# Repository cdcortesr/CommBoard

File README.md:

## Communication Board (CommBoard)
<picture>
  <source media="(prefers-color-scheme: dark)" srcset="https://i.imgur.com/UVEQvyd.jpeg">
  <source media="(prefers-color-scheme: light)" srcset="https://i.imgur.com/UVEQvyd.jpeg">
  
</picture>

Self-built serial communication board based on an STM32 microcontroller, designed for embedded systems applications. Key features and technical details include:

• Communication Interfaces:

&nbsp;&nbsp;&nbsp;&nbsp;• I²C (Inter-Integrated Circuit) interface for peripheral connectivity.

&nbsp;&nbsp;&nbsp;&nbsp;• UART (Universal Asynchronous Receiver-Transmitter) for serial communication.

&nbsp;&nbsp;&nbsp;&nbsp;• JTAG interface for in-circuit programming and debugging.

&nbsp;&nbsp;&nbsp;&nbsp;• USB for data transfer and power input.

• PCB Design and Manufacturing:

&nbsp;&nbsp;&nbsp;&nbsp;• Dual-layer printed circuit board (PCB) designed using KiCad.

&nbsp;&nbsp;&nbsp;&nbsp;• Fabricated by JLCPCB (PCB manufacturer).

&nbsp;&nbsp;&nbsp;&nbsp;• Self-assembled using a combination of reflow oven soldering and manual hand soldering techniques.

• Power Supply:

&nbsp;&nbsp;&nbsp;&nbsp;• Powered via USB connection.

&nbsp;&nbsp;&nbsp;&nbsp;• Integrated Low Dropout Regulator (LDO) for stable voltage supply.

This project demonstrates proficiency in hardware design, embedded programming, and hands-on electronics assembly.

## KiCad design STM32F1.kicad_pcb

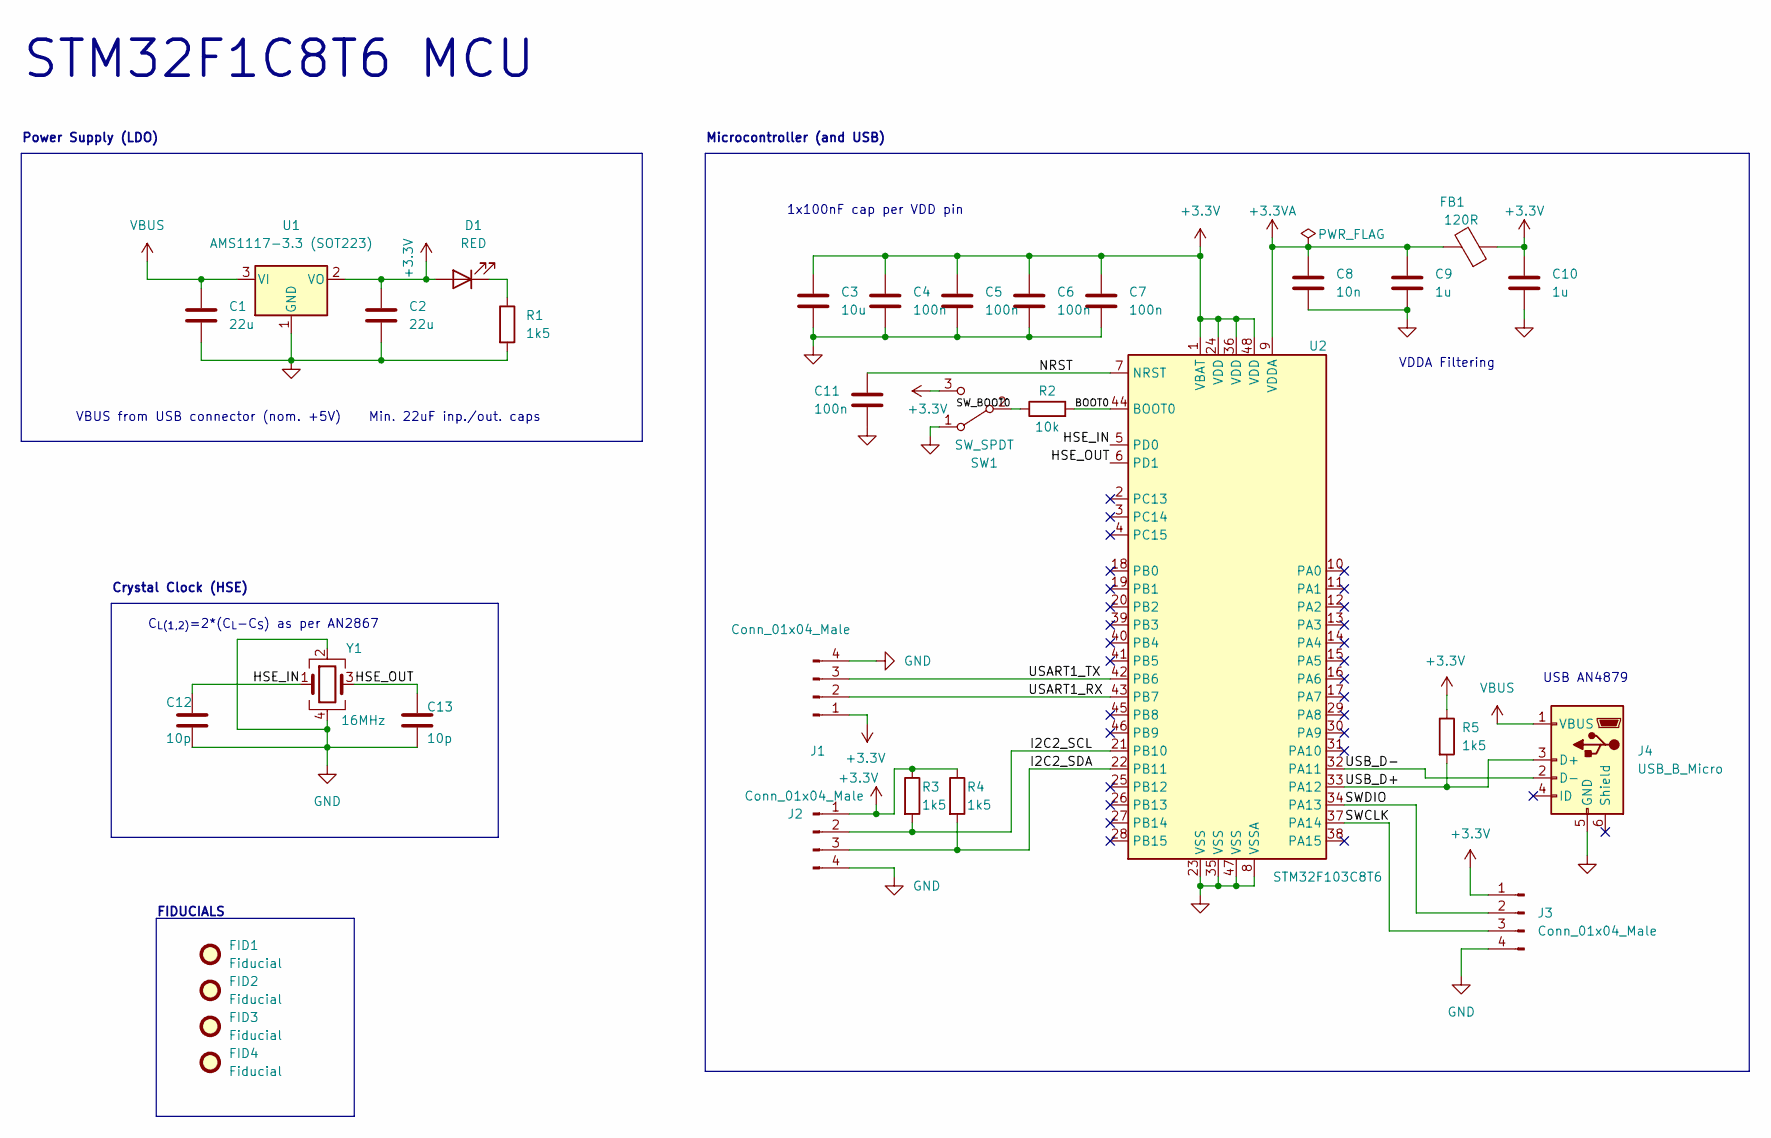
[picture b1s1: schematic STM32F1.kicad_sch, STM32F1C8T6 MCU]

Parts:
C1, C2: 22u; C_0805_2012Metric
C3: 10u; C_0603_1608Metric
C4, C5, C6, C7, C11: 100n; C_0402_1005Metric
C8: 10n; C_0603_1608Metric
C9, C10: 1u; C_0402_1005Metric
C12, C13: 10p; C_0402_1005Metric
D1: RED; LED_0603_1608Metric
FB1: 120R; L_0201_0603Metric
FID1, FID2, FID3, FID4: Fiducial; Fiducial_1mm_Mask2mm
J1, J2, J3: Conn_01x04_Male; PinHeader_1x04_P2.54mm_Vertical
J4: USB_B_Micro; USB_Micro-B_Wuerth_629105150521
R1, R3, R4, R5: 1k5; R_0402_1005Metric
R2: 10k; R_0402_1005Metric
SW1: SW_SPDT; SW_JS102011SAQN
U1: AMS1117-3.3 (SOT223); SOT-223-3_TabPin2
U2: STM32F103C8T6; LQFP-48_7x7mm_P0.5mm
Y1: 16MHz; Crystal_SMD_3225-4Pin_3.2x2.5mm

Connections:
+3.3VA: C8.1, C9.1, FB1.2, U2.9 (VDDA)
+3V3: C2.1, C3.1, C4.1, C5.1, C6.1, C7.1, C10.1, D1.2 (A), FB1.1, J1.1, J2.1, J3.1, R3.1, R4.1, R5.1, SW1.3 (C), U1.2 (VO), U2.1 (VBAT), U2.24 (VDD), U2.36 (VDD), U2.48 (VDD)
/BOOT0: R2.2, U2.44 (BOOT0)
/HSE_IN: C12.1, U2.5 (PD0), Y1.1
/HSE_OUT: C13.1, U2.6 (PD1), Y1.3
/I2C2_SCL: J2.2, R3.2, U2.21 (PB10)
/I2C2_SDA: J2.3, R4.2, U2.22 (PB11)
/NRST: C11.1, U2.7 (NRST)
/SWCLK: J3.3, U2.37 (PA14)
/SWDIO: J3.2, U2.34 (PA13)
/SW_BOOT0: R2.1, SW1.2 (B)
/USART1_RX: J1.2, U2.43 (PB7)
/USART1_TX: J1.3, U2.42 (PB6)
/USB_D+: J4.3 (D+), R5.2, U2.33 (PA12)
/USB_D-: J4.2 (D-), U2.32 (PA11)
GND: C1.2, C2.2, C3.2, C4.2, C5.2, C6.2, C7.2, C8.2, C9.2, C10.2, C11.2, C12.2, C13.2, J1.4, J2.4, J3.4, J4.5 (GND), R1.2, SW1.1 (A), U1.1 (GND), U2.8 (VSSA), U2.23 (VSS), U2.35 (VSS), U2.47 (VSS), Y1.2, Y1.4
unnamed: D1.1 (K), R1.1
VBUS: C1.1, J4.1 (VBUS), U1.3 (VI)

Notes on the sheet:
1x100nF cap per VDD pin
Power Supply (LDO)
${TITLE}
VDDA Filtering
Crystal Clock (HSE)
FIDUCIALS
Microcontroller (and USB)
VBUS from USB connector (nom. +5V) Min. 22uF inp./out. caps
C_{L(1,2)}=2*(C_{L}-C_{S}) as per AN2867
USB AN4879

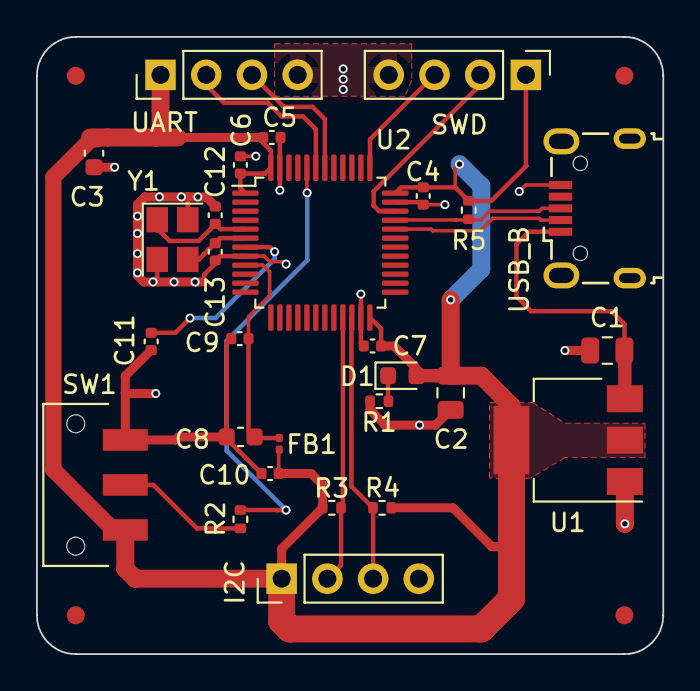
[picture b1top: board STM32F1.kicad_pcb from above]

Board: 2 copper layers, 34.8 x 34.3 mm, 32 parts (0 on the bottom side), 18 nets.

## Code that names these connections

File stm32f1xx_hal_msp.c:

/* USER CODE BEGIN Header */
/**
  ******************************************************************************
  * @file         stm32f1xx_hal_msp.c
  * @brief        This file provides code for the MSP Initialization
  *               and de-Initialization codes.
  ******************************************************************************
  * @attention
  *
  * Copyright (c) 2023 STMicroelectronics.
  * All rights reserved.
  *
  * This software is licensed under terms that can be found in the LICENSE file
  * in the root directory of this software component.
  * If no LICENSE file comes with this software, it is provided AS-IS.
  *
  ******************************************************************************
  */
/* USER CODE END Header */

/* Includes ------------------------------------------------------------------*/
#include "main.h"

/* USER CODE BEGIN Includes */

/* USER CODE END Includes */

/* Private typedef -----------------------------------------------------------*/
/* USER CODE BEGIN TD */

/* USER CODE END TD */

/* Private define ------------------------------------------------------------*/
/* USER CODE BEGIN Define */

/* USER CODE END Define */

/* Private macro -------------------------------------------------------------*/
/* USER CODE BEGIN Macro */

/* USER CODE END Macro */

/* Private variables ---------------------------------------------------------*/
/* USER CODE BEGIN PV */

/* USER CODE END PV */

/* Private function prototypes -----------------------------------------------*/
/* USER CODE BEGIN PFP */

/* USER CODE END PFP */

/* External functions --------------------------------------------------------*/
/* USER CODE BEGIN ExternalFunctions */

/* USER CODE END ExternalFunctions */

/* USER CODE BEGIN 0 */

/* USER CODE END 0 */
/**
  * Initializes the Global MSP.
  */
void HAL_MspInit(void)
{
  /* USER CODE BEGIN MspInit 0 */

  /* USER CODE END MspInit 0 */

  __HAL_RCC_AFIO_CLK_ENABLE();
  __HAL_RCC_PWR_CLK_ENABLE();

  /* System interrupt init*/

  /** NOJTAG: JTAG-DP Disabled and SW-DP Enabled
  */
  __HAL_AFIO_REMAP_SWJ_NOJTAG();

  /* USER CODE BEGIN MspInit 1 */

  /* USER CODE END MspInit 1 */
}

/**
* @brief I2C MSP Initialization
* This function configures the hardware resources used in this example
* @param hi2c: I2C handle pointer
* @retval None
*/
void HAL_I2C_MspInit(I2C_HandleTypeDef* hi2c)
{
  GPIO_InitTypeDef GPIO_InitStruct = {0};
  if(hi2c->Instance==I2C2)
  {
  /* USER CODE BEGIN I2C2_MspInit 0 */

  /* USER CODE END I2C2_MspInit 0 */

    __HAL_RCC_GPIOB_CLK_ENABLE();
    /**I2C2 GPIO Configuration
    PB10     ------> I2C2_SCL
    PB11     ------> I2C2_SDA
    */
    GPIO_InitStruct.Pin = GPIO_PIN_10|GPIO_PIN_11;
    GPIO_InitStruct.Mode = GPIO_MODE_AF_OD;
    GPIO_InitStruct.Speed = GPIO_SPEED_FREQ_HIGH;
    HAL_GPIO_Init(GPIOB, &GPIO_InitStruct);

    /* Peripheral clock enable */
    __HAL_RCC_I2C2_CLK_ENABLE();
  /* USER CODE BEGIN I2C2_MspInit 1 */

  /* USER CODE END I2C2_MspInit 1 */
  }

}

/**
* @brief I2C MSP De-Initialization
* This function freeze the hardware resources used in this example
* @param hi2c: I2C handle pointer
* @retval None
*/
void HAL_I2C_MspDeInit(I2C_HandleTypeDef* hi2c)
{
  if(hi2c->Instance==I2C2)
  {
  /* USER CODE BEGIN I2C2_MspDeInit 0 */

  /* USER CODE END I2C2_MspDeInit 0 */
    /* Peripheral clock disable */
    __HAL_RCC_I2C2_CLK_DISABLE();

    /**I2C2 GPIO Configuration
    PB10     ------> I2C2_SCL
    PB11     ------> I2C2_SDA
    */
    HAL_GPIO_DeInit(GPIOB, GPIO_PIN_10);

    HAL_GPIO_DeInit(GPIOB, GPIO_PIN_11);

  /* USER CODE BEGIN I2C2_MspDeInit 1 */

  /* USER CODE END I2C2_MspDeInit 1 */
  }

}

/**
* @brief UART MSP Initialization
* This function configures the hardware resources used in this example
* @param huart: UART handle pointer
* @retval None
*/
void HAL_UART_MspInit(UART_HandleTypeDef* huart)
{
  GPIO_InitTypeDef GPIO_InitStruct = {0};
  if(huart->Instance==USART1)
  {
  /* USER CODE BEGIN USART1_MspInit 0 */

  /* USER CODE END USART1_MspInit 0 */
    /* Peripheral clock enable */
    __HAL_RCC_USART1_CLK_ENABLE();

    __HAL_RCC_GPIOB_CLK_ENABLE();
    /**USART1 GPIO Configuration
    PB6     ------> USART1_TX
    */
    GPIO_InitStruct.Pin = GPIO_PIN_6;
    GPIO_InitStruct.Mode = GPIO_MODE_AF_OD;
    GPIO_InitStruct.Speed = GPIO_SPEED_FREQ_HIGH;
    HAL_GPIO_Init(GPIOB, &GPIO_InitStruct);

    __HAL_AFIO_REMAP_USART1_ENABLE();

  /* USER CODE BEGIN USART1_MspInit 1 */

  /* USER CODE END USART1_MspInit 1 */
  }

}

/**
* @brief UART MSP De-Initialization
* This function freeze the hardware resources used in this example
* @param huart: UART handle pointer
* @retval None
*/
void HAL_UART_MspDeInit(UART_HandleTypeDef* huart)
{
  if(huart->Instance==USART1)
  {
  /* USER CODE BEGIN USART1_MspDeInit 0 */

  /* USER CODE END USART1_MspDeInit 0 */
    /* Peripheral clock disable */
    __HAL_RCC_USART1_CLK_DISABLE();

    /**USART1 GPIO Configuration
    PB6     ------> USART1_TX
    */
    HAL_GPIO_DeInit(GPIOB, GPIO_PIN_6);

  /* USER CODE BEGIN USART1_MspDeInit 1 */

  /* USER CODE END USART1_MspDeInit 1 */
  }

}

/* USER CODE BEGIN 1 */

/* USER CODE END 1 */

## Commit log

2025-06-01 Included main.c
